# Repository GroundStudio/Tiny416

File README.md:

GroundStudio Tiny416
====================================

Get it from [ardushop.ro](https://ardushop.ro/ro/home/2714-groundstudio-tiny-416.html)

Explore all the GroundStudio products at [GroundStudio.ro](https://groundstudio.ro/)

Description
-------------------
Breakout board for ATtiny416 chip with 4kB Flash, 256B SRAM, 128B EEPROM, 17x GPIO pins, 12x ADC pins and 2x I2C_3V3 connectors.

Contents
-------------------

* [/Documentation](https://github.com/GroundStudio/Tiny416/tree/main/Documentation) -- Pinout.
* [/Hardware](https://github.com/GroundStudio/Tiny416/tree/main/Hardware) -- Schematics, layout.

Versions
-------------------
*(Not all tags shown)*

- [REV 0.0.2]

License
-------------------

This is released under the [Attribution-ShareAlike 4.0 International (CC BY-SA 4.0)](https://creativecommons.org/licenses/by-sa/4.0/) license.
**You are welcome to use this for commercial purposes.**

Please consider contributing back to this project or others to help the open-source hardware community continue to thrive and grow!

Certifications:

[Open Source Hardware Association](https://certification.oshwa.org/ro000027.html)   
   
[
](https://certification.oshwa.org/ro000027.html)

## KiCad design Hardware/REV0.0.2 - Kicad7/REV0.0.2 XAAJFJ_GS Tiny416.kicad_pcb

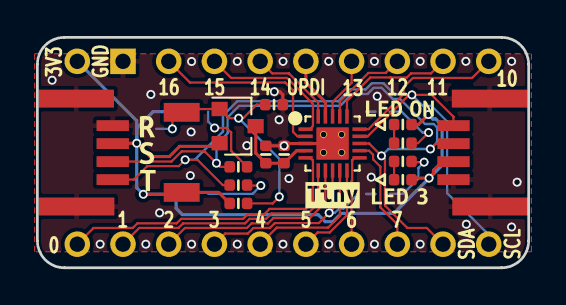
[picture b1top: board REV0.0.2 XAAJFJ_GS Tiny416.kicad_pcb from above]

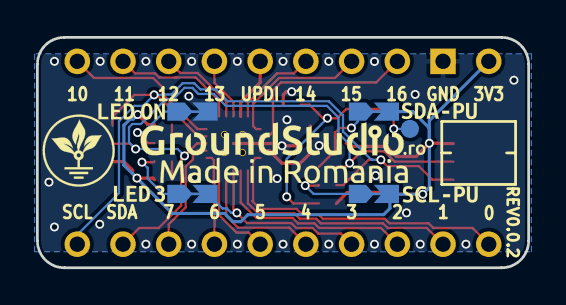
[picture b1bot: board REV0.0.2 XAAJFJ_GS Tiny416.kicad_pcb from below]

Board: 2 copper layers, 27.3 x 12.8 mm, 36 parts (12 on the bottom side), 28 nets.

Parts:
C1: C_0402_10uF_10V; C_0402_alt
C4: C_0402_100nF_16V; C_0402_alt
J2, J3: PinHeader_1x10_P2.54_V_M; PinHeader_1x10_P2.54mm_Vertical_Male
J4, J5, J7, J9: SolderJumper_NC
J10, J11: SH_1x04_P1.0_H; SH__1x04_P1.00mm_Horizontal
LED1: LED_0402_GREEN; LED_0402_alt
LED2: LED_0402_RED; LED_0402_alt
Q1: SOT-23_IRLML6402; SOT-23
R2, R6: R_0402_5.1k; R_0402_alt
R3: R_0402_1.5k; R_0402_alt
R4: R_0402_100k; R_0402_alt
R5, R7: R_0402_10k; R_0402_alt
SW1: TS342A2P-WZ
TP1: Reset Switch; TestPoint
U1: QFN-20-1EP_3x3_P0.4_ATTINY416; QFN-20-1EP_3x3mm_P0.4mm_EP1.7x1.7mm
kibuzzard-63A45BC8: G***; kibuzzard-63A45BC8
kibuzzard-63A56FA7: G***; kibuzzard-63A56FA7
kibuzzard-63A56FD0: G***; kibuzzard-63A56FD0
kibuzzard-63BFB52D, kibuzzard-63BFB52D#2: G***; kibuzzard-63BFB52D
kibuzzard-63BFB55B: G***; kibuzzard-63BFB55B
kibuzzard-63BFB535, kibuzzard-63BFB535#2: G***; kibuzzard-63BFB535
kibuzzard-642ECCB9: G***; kibuzzard-642ECCB9
kibuzzard-642ECCC4: G***; kibuzzard-642ECCC4
kibuzzard-642ECCCC: G***; kibuzzard-642ECCCC
kibuzzard-64368A54: G***; kibuzzard-64368A54
kibuzzard-64368AB1: G***; kibuzzard-64368AB1
kibuzzard-64368AD5: G***; kibuzzard-64368AD5

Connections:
0_SS_ADC4: J2.1, U1.5 (PA4)
1_ADC5: J2.2, U1.6 (PA5)
2_DAC0_ADC6: J2.3, U1.7 (PA6)
3_ADC7: J2.4, J5.2, U1.8 (PA7)
4_ADC8: J2.5, U1.9 (PB5)
5_ADC9: J2.6, U1.10 (PB4)
6_RxD: J2.7, U1.11 (PB3)
7_TxD: J2.8, U1.12 (PB2)
10: J3.10, U1.15 (PC0)
11: J3.9, U1.16 (PC1)
12: J3.8, U1.17 (PC2)
13: J3.7, U1.18 (PC3)
14_MOSI_ADC1: J3.5, U1.20 (PA1)
15_MISO_ADC2: J3.4, U1.1 (PA2)
16_SCK_ADC3: J3.3, U1.2 (PA3)
+3V3: J3.1, J7.2, J9.2, J10.2 (3V3), J11.2 (3V3), LED1.2 (A), LED2.2 (A), Q1.2 (S), R4.1, SW1.1
GND: C1.1, C4.2, J3.2, J4.2, J10.0 (SHIELD), J10.1 (GND), J11.0 (SHIELD), J11.1 (GND), R6.2, U1.3 (GND), U1.21 (GND)
unnamed: J7.1, R5.1
unnamed: J9.1, R7.1
unnamed: LED1.1 (K), R2.1
unnamed: LED2.1 (K), R3.1
unnamed: Q1.1 (G), R4.2, R6.1, SW1.2, TP1.1
unnamed: J4.1, R2.2
unnamed: J5.1, R3.2
SCL_ADC11: J2.10, J10.4 (SCL), J11.4 (SCL), R5.2, U1.14 (PB0)
SDA_ADC10: J2.9, J10.3 (SDA), J11.3 (SDA), R7.2, U1.13 (PB1)
UPDI: J3.6, U1.19 (~RESET/PA0)
VCC: C1.2, C4.1, Q1.3 (D), U1.4 (VCC)

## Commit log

2024-03-06 - initial commit
